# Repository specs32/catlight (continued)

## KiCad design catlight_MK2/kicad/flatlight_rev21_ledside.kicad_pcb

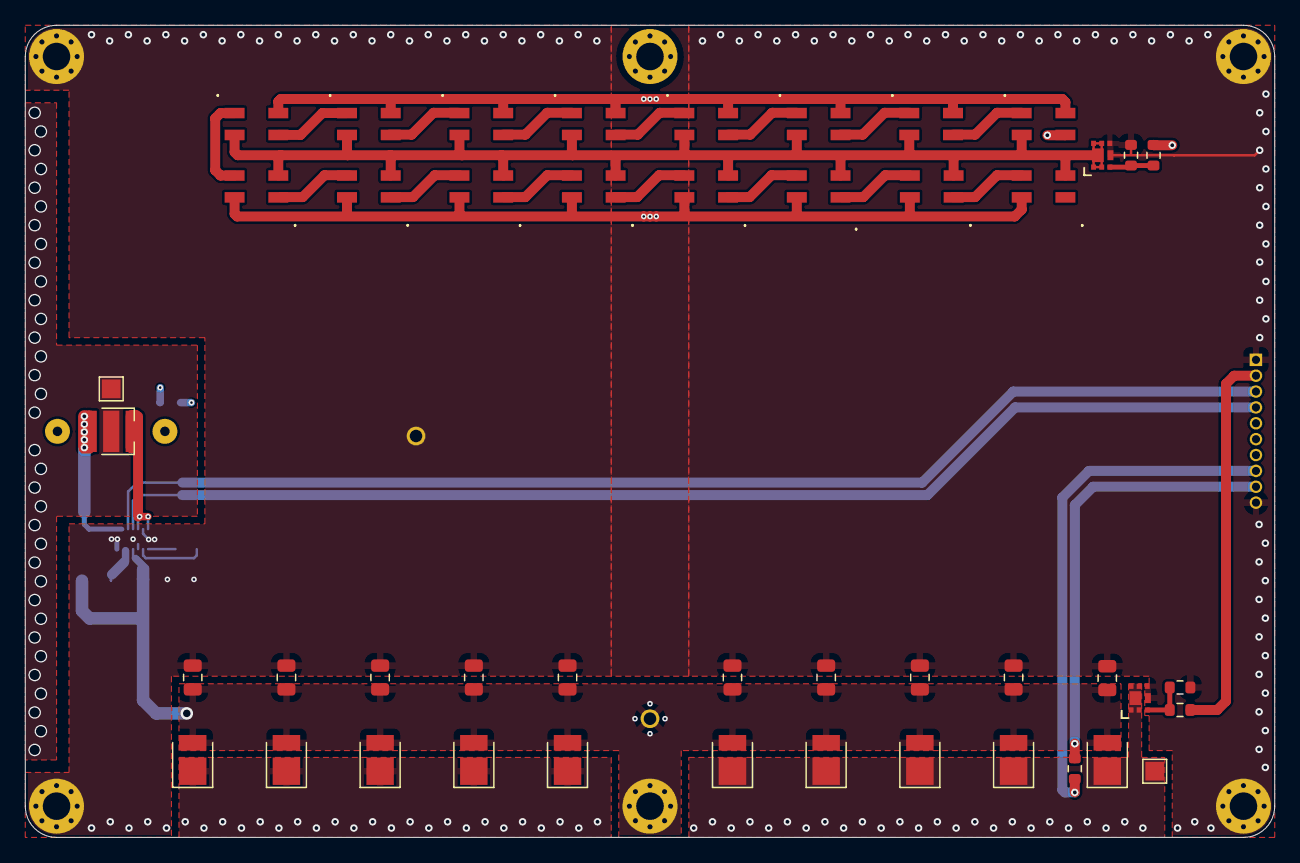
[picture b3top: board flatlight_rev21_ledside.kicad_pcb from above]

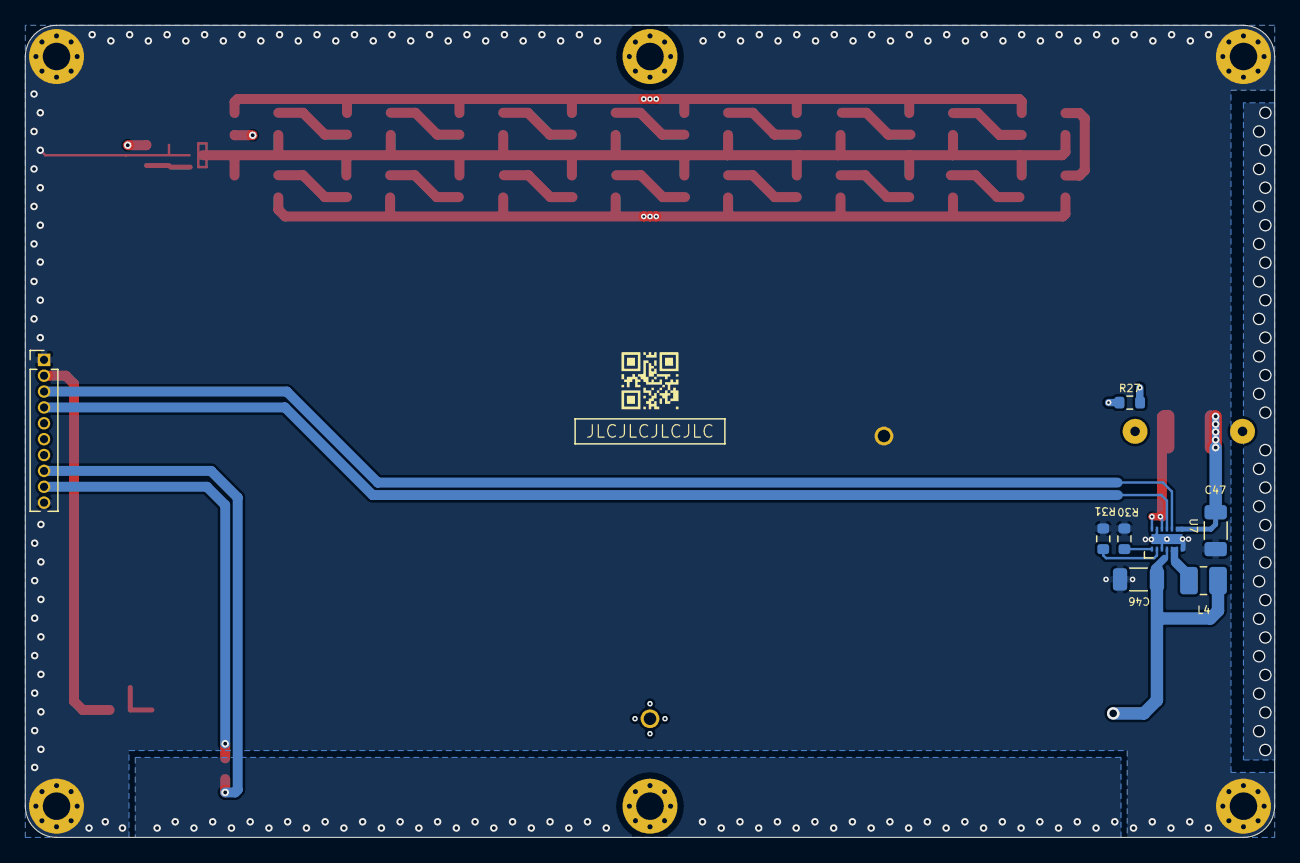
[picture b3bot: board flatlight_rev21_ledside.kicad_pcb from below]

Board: 4 copper layers, 100.0 x 65.0 mm, 67 parts (10 on the bottom side), 35 nets.

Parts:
C30, C31, C32, C33, C34, C35, C36, C37, C38, C39: 10µF; C_0805_2012Metric
C46: 22µF; C_1206_3216Metric
C47: 10µF; C_1206_3216Metric
D3, D4, D5, D6, D7, D8, D9, D10, D11, D12, D13, D14, D15, D16, D17, D18: SK6812MINI; LED_SK6812MINI
D19, D20, D21, D22, D23, D24, D25, D26, D27, D28: LED; LED_PLCC_2835
D35: LED_Cree_XPP; LED_Cree-XHP35
H7: thole1; plated_hole_1mm
H14: thole8; plated_hole_1mm
H15, H16, H17, H18, H19, H20: MountingHole_Pad; MountingHole_2.2mm_M2_Pad_Via
J4: B2B_ledside; PinHeader_1x10_P1.27mm_Vertical
L4: 1µH; L_1008_2520Metric_Pad1.43x2.20mm_HandSolder
Q3, Q4: DMN2022-UFDF7; U-DFN2020-6 (Type F)
R24, R28: 1kΩ; R_0603_1608Metric
R25, R29: 1MΩ; R_0603_1608Metric
R26, R27: NTC 10 kΩ; R_0603_1608Metric
R30: 37.5kΩ; R_0603_1608Metric
R31: 12kΩ; R_0603_1608Metric
TP9, TP10: TestPoint; TestPoint_Pad_1.5x1.5mm
U7: LDRV_DIO5180; DFN-14-2x3mm
lense1: Lense_Mount; LENS_LEDIL_C12491_siri_diff
logo1: logo_qrtag; logo_QR_url_git_catlight
logo5: logo_JLC; JLC-SERIAL
logo9: logo_LWarn; logo_lightwarn_large
logo10: logo_CATLIGHT; logo_catlightMK2_small

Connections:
+3V3: J4.9, R26.1, R27.1
GND: C30.2, C31.2, C32.2, C33.2, C34.2, C35.2, C36.2, C37.2, C38.2, C39.2, C46.1, C47.1, H14.1, H17.1, H18.1, H19.1, H20.1, J4.1, J4.10, Q3.2 (S), Q4.2 (S), R25.1, R29.1, R30.1, R31.1, U7.3 (AGND), U7.7 (PGND), U7.13 (AGND), U7.15 (AGND)
LS_FLASH_EN: J4.3, U7.10 (ENF)
LS_JS_LED_NTC: J4.8, R26.2
LS_LED_PWM: J4.2, R28.1
LS_PWM_PWR: D19.1 (K), D20.1 (K), D21.1 (K), D22.1 (K), D23.1 (K), D24.1 (K), D25.1 (K), D26.1 (K), D27.1 (K), D28.1 (K), Q4.1 (D), TP9.1
LS_SYS: C30.1, C31.1, C32.1, C33.1, C34.1, C35.1, C36.1, C37.1, C38.1, C39.1, C46.2, D3.4 (VDD), D4.4 (VDD), D5.4 (VDD), D6.4 (VDD), D7.4 (VDD), D8.4 (VDD), D9.4 (VDD), D10.4 (VDD), D11.4 (VDD), D12.4 (VDD), D13.4 (VDD), D14.4 (VDD), D15.4 (VDD), D16.4 (VDD), D17.4 (VDD), D18.4 (VDD), D19.2 (A), D20.2 (A), D21.2 (A), D22.2 (A), D23.2 (A), D24.2 (A), D25.2 (A), D26.2 (A), D27.2 (A), D28.2 (A), H7.1, H15.1, H16.1, L4.1, U7.4 (VIN)
LS_TORCH_EN: J4.4, U7.11 (ENM)
LS_WS_LDAT: D3.3 (DIN), J4.5
LS_WS_POWER: J4.6, R24.2
LS_XP_LED_NTC: J4.7, R27.2
unnamed: C47.2, D35.2 (K), U7.8 (VOUT), U7.9 (VOUT)
unnamed: D3.1 (DOUT), D4.3 (DIN)
unnamed: D4.1 (DOUT), D5.3 (DIN)
unnamed: D5.1 (DOUT), D6.3 (DIN)
unnamed: D6.1 (DOUT), D7.3 (DIN)
unnamed: D7.1 (DOUT), D8.3 (DIN)
unnamed: D8.1 (DOUT), D9.3 (DIN)
unnamed: D10.1 (DOUT), D11.3 (DIN)
unnamed: D9.1 (DOUT), D10.3 (DIN)
unnamed: D11.1 (DOUT), D12.3 (DIN)
unnamed: D12.1 (DOUT), D13.3 (DIN)
unnamed: D13.1 (DOUT), D14.3 (DIN)
unnamed: D14.1 (DOUT), D15.3 (DIN)
unnamed: D15.1 (DOUT), D16.3 (DIN)
unnamed: D16.1 (DOUT), D17.3 (DIN)
unnamed: D17.1 (DOUT), D18.3 (DIN)
unnamed: D35.1 (A), U7.12 (D1), U7.14 (D2)
unnamed: L4.2, U7.5 (SW), U7.6 (SW)
unnamed: Q3.3 (G), R24.1, R25.2
unnamed: Q4.3 (G), R28.2, R29.2
unnamed: R30.2, U7.1 (RSETM)
unnamed: R31.2, U7.2 (RSETF)
PAD: D35.3 (PAD), TP10.1
WS_GNDBUS: D3.2 (VSS), D4.2 (VSS), D5.2 (VSS), D6.2 (VSS), D7.2 (VSS), D8.2 (VSS), D9.2 (VSS), D10.2 (VSS), D11.2 (VSS), D12.2 (VSS), D13.2 (VSS), D14.2 (VSS), D15.2 (VSS), D16.2 (VSS), D17.2 (VSS), D18.2 (VSS), Q3.1 (D)

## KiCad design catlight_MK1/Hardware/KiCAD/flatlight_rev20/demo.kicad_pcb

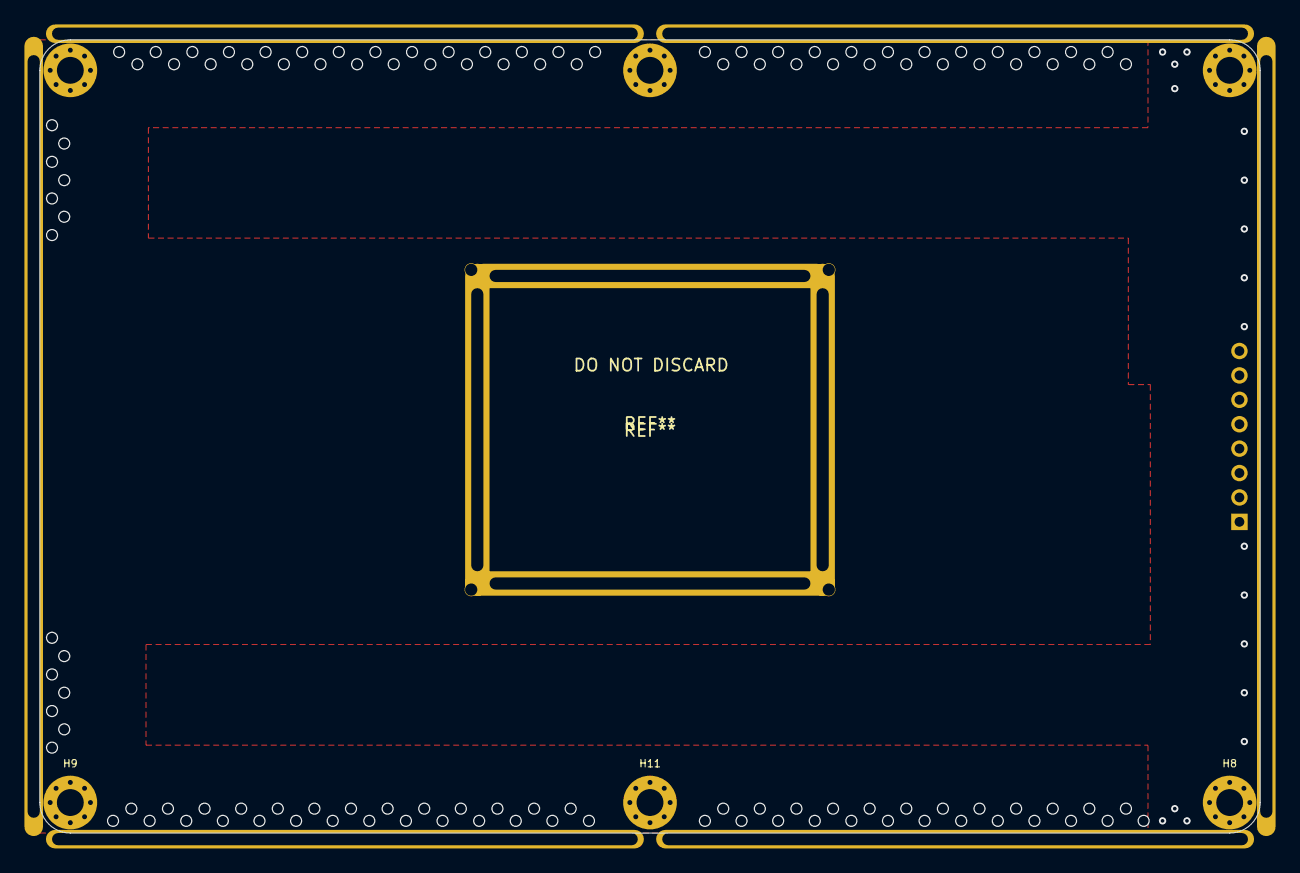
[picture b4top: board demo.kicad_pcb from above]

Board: 4 copper layers, 100.0 x 65.0 mm, 7 parts (1 on the bottom side), 2 nets.

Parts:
H7, H8, H9, H10, H11, H12: MountingHole_Pad; MountingHole_2.2mm_M2_Pad_Via
J5: Conn_01x08_Female; PinHeader_1x08_P2.00mm_Vertical

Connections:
+BATT: H7.1, H11.1
GND: H8.1, H9.1, H10.1, H12.1, J5.1, J5.5

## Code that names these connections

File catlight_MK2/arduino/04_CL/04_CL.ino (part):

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

// CHARGER PINS
#define INOK 35
#define ENBST 33
#define CHGSTAT 34


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  pinMode(BUTTON_ENTER, INPUT_PULLUP);

  //define CHARGER pins
  pinMode(ENBST, OUTPUT);           // boost  function
  digitalWrite(ENBST, LOW);         // off by default
  pinMode(INOK, INPUT_PULLUP);      // input source detection high = good | high = boost | off = no VBUS IO
  pinMode(CHGSTAT, INPUT_PULLUP);   // charger status 500ms pulse = charging | off=done

  // define Pins for NEOPIXEL PWR MOSFET and setup pixels
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  u8g2_for_adafruit_gfx.setForegroundColor(ST77XX_BLACK);      // apply Adafruit GFX color

  // Set ADC Gain and Res
  analogSetPinAttenuation(1, ADC_11db); // ADC_BATV (BAT divider)
  analogSetPinAttenuation(2, ADC_11db); // NTC_PWMLED (top between the LEDS)
  analogSetPinAttenuation(3, ADC_11db); // NTC_BAT / XP_LED (bottom NTC)

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
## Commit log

2021-07-19 catlight - first commit
2021-07-20 catlight - MK1
2021-10-16 catlight - MK2
2021-10-16 Add files via upload
    platformio override to compile with WLED 0.13.0-b2 (!)
